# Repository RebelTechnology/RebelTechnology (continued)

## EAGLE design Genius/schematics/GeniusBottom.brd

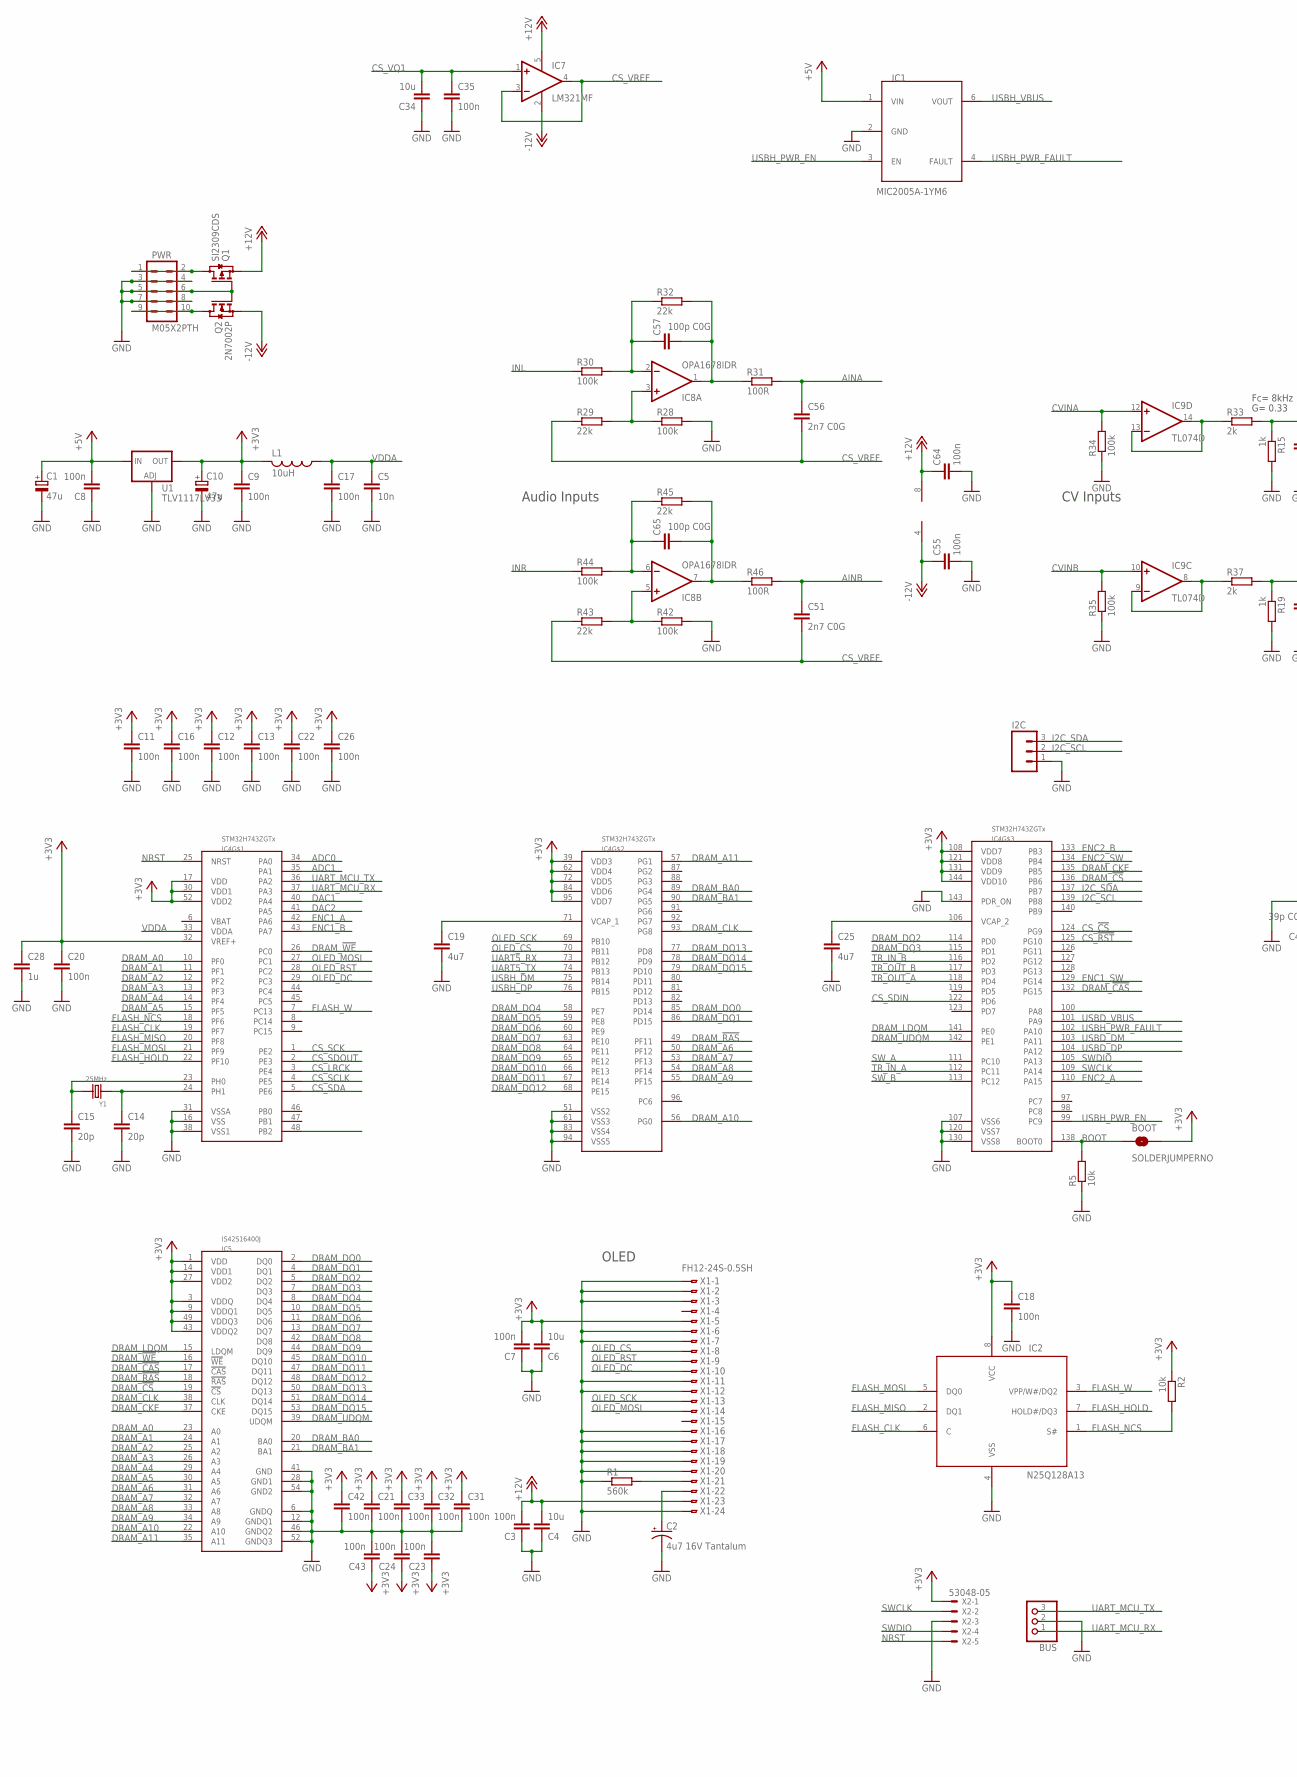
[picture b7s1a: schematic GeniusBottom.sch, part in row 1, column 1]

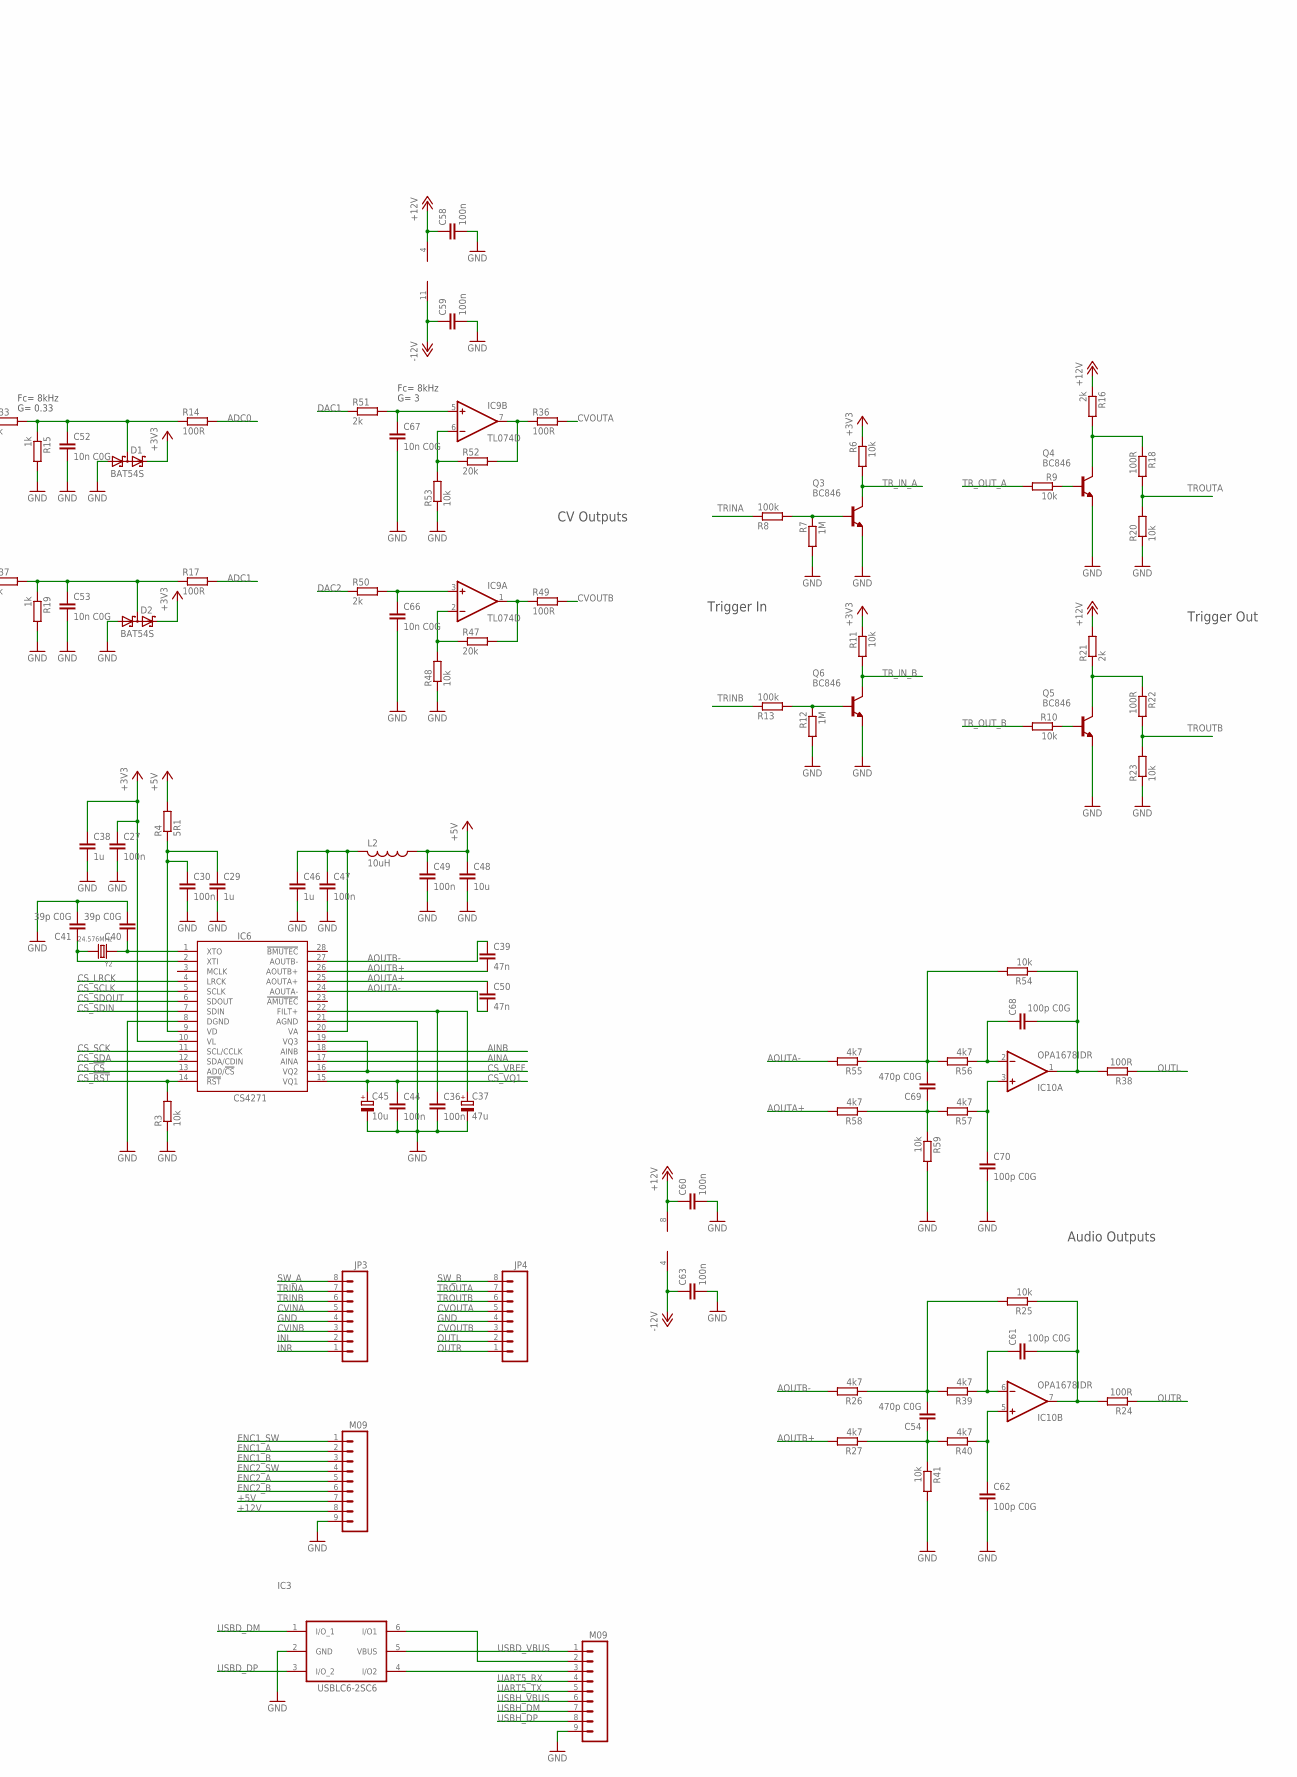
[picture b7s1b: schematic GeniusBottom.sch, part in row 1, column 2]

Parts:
BOOT: SOLDERJUMPERNO; SJ_2S-NO
BUS: CON-JST-1X03PH-TH; JST-B3B-PH-KL
C1, C10, C37: 47u; CPOL-5
C2: 4u7 16V Tantalum; EIA3216
C3, C7, C8, C9, C11, C12, C13, C16, C17, C18, C20, C21, C22, C23, C24, C26, C27, C30, C31, C32, C33, C35, C36, C42, C43, C44, C47, C49, C55, C58, C59, C60, C63, C64: 100n; C0603
C4, C6, C34, C48: 10u; C1206
C5: 10n; C0603
C14, C15: 20p; C0603
C19, C25: 4u7; C0603
C28, C29, C38, C46: 1u; C0603
C39, C50: 47n; C0603
C40, C41: 39p C0G; C0603
C45: 10u; CPOL-5
C51, C56: 2n7 C0G; C0603
C52, C53, C66, C67: 10n C0G; C0603
C54, C69: 470p C0G; C0603
C57, C61, C62, C65, C68, C70: 100p C0G; C0603
D1, D2: BAT54S; SOT23
I2C: M03PTH; 1X03
IC1: MIC2005A-1YM6; SOT23-6
IC2: N25Q128A13; SO8W
IC3: USBLC6-2SC6; SOT-23-6L
IC4: STM32H743ZGTx; QFP50P2200X2200X160-144N
IC5: IS42S16400J; TSOP54-400
IC6: CS4271; TSSOP28-0.65-9.7X4.4MM
IC7: LM321MF; SOT23-5
IC8, IC10: OPA1678IDR; SO08
IC9: TL074D; SO14
JP1, JP2: M09; 1X09
JP3, JP4: M081X08; 1X08
L1, L2: 10uH; 0603
PWR: M05X2PTH; AVR_ICSP
Q1: SI2309CDS; SOT23
Q2: 2N7002P; SOT23
Q3, Q4, Q5, Q6: BC846; SOT23
R1: 560k; 0603
R2, R3, R5, R6, R9, R10, R11, R20, R23, R25, R41, R48, R53, R54, R59: 10k; 0603
R4: 5R1; 0603
R7, R12: 1M; 0603
R8, R13, R28, R30, R34, R35, R42, R44: 100k; 0603
R14, R17, R18, R22, R24, R31, R36, R38, R46, R49: 100R; 0603
R15, R19: 1k; 0603
R16, R21, R33, R37, R50, R51: 2k; 0603
R26, R27, R39, R40, R55, R56, R57, R58: 4k7; 0603
R29, R32, R43, R45: 22k; 0603
R47, R52: 20k; 0603
U1: TLV1117LV33; SOT223
X1: FH12-24S-0.5SH
X2: 53048-05
Y1: 25MHz; X2-SMD-5.0X3.2X1.3MM
Y2: 24.576MHz; X2-SMD-5.0X3.2X1.3MM

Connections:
+3.3V: BOOT.2, C6.2, C7.2, C9.1, C10.+, C11.1, C12.1, C13.1, C16.1, C18.1, C20.1, C21.1, C22.1, C23.1, C24.1, C26.1, C27.1, C28.1, C31.1, C32.1, C33.1, C38.1, C42.1, C43.1, D1.2 (C2), D2.2 (C2), IC2.8 (VCC), IC4.17 (VDD), IC4.30 (VDD1), IC4.32 (VREF+), IC4.39 (VDD3), IC4.52 (VDD2), IC4.62 (VDD4), IC4.72 (VDD5), IC4.84 (VDD6), IC4.95 (VDD7), IC4.108 (VDD7), IC4.121 (VDD8), IC4.131 (VDD9), IC4.144 (VDD10), IC5.1 (VDD), IC5.3 (VDDQ), IC5.9 (VDDQ1), IC5.14 (VDD1), IC5.27 (VDD2), IC5.43 (VDDQ2), IC5.49 (VDDQ3), IC6.10 (VL), L1.2, R2.1, R6.1, R11.1, U1.4 (OUT), X1.5, X2.1
+5V: C1.+, C8.2, C48.1, C49.1, IC1.1 (VIN), JP2.7, L2.1, R4.2, U1.3 (IN)
+12V: C3.2, C4.2, C58.1, C60.1, C64.1, IC7.5 (V+), IC8.8 (V+), IC9.4 (V+), IC10.8 (V+), JP2.8, Q1.2 (S), R16.1, R21.2, X1.23
-12V: C55.1, C59.1, C63.1, IC7.2 (V-), IC8.4 (V-), IC9.11 (V-), IC10.4 (V-), Q2.2 (S)
ADC0: IC4.34 (PA0), R14.2
ADC1: IC4.35 (PA1), R17.2
AINA: C56.1, IC6.17 (AINA), R31.2
AINB: C51.1, IC6.18 (AINB), R46.2
ANALOG_OUTA: C68.2, IC10.1 (OUT), R38.2, R54.1
ANALOG_OUTB: C61.2, IC10.7 (OUT), R24.2, R25.1
AOUTA+: C50.1, IC6.25 (AOUTA+), R58.2
AOUTA-: C50.2, IC6.24 (AOUTA-), R55.2
AOUTB+: C39.2, IC6.26 (AOUTB+), R27.2
AOUTB-: C39.1, IC6.27 (AOUTB-), R26.2
BOOT: BOOT.1, IC4.138 (BOOT0), R5.2
CS_!CS: IC4.124 (PG9), IC6.13 (AD0/!CS)
CS_!RST: IC4.125 (PG10), IC6.14 (!RST), R3.2
CS_LRCK: IC4.3 (PE4), IC6.4 (LRCK)
CS_SCK: IC4.1 (PE2), IC6.11 (SCL/CCLK)
CS_SCLK: IC4.4 (PE5), IC6.5 (SCLK)
CS_SDA: IC4.5 (PE6), IC6.12 (SDA/CDIN)
CS_SDIN: IC4.122 (PD6), IC6.7 (SDIN)
CS_SDOUT: IC4.2 (PE3), IC6.6 (SDOUT)
CS_VQ1: C34.2, C35.1, C44.1, C45.+, IC6.15 (VQ1), IC7.1 (+IN)
CS_VREF: C51.2, C56.2, IC6.16 (VQ2), IC6.19 (VQ3), IC7.3 (-IN), IC7.4 (OUT), R29.1, R43.1
CVINA: IC9.12 (+IN), JP3.5, R34.2
CVINB: IC9.10 (+IN), JP3.3, R35.2
CVOUTA: JP4.5, R36.2
CVOUTB: JP4.3, R49.2
DAC1: IC4.40 (PA4), R51.1
DAC2: IC4.41 (PA5), R50.1
DRAM_!CAS: IC4.132 (PG15), IC5.17 (!CAS)
DRAM_!CS: IC4.136 (PB6), IC5.19 (!CS)
DRAM_!RAS: IC4.49 (PF11), IC5.18 (!RAS)
DRAM_!WE: IC4.26 (PC0), IC5.16 (!WE)
DRAM_A0: IC4.10 (PF0), IC5.23 (A0)
DRAM_A1: IC4.11 (PF1), IC5.24 (A1)
DRAM_A2: IC4.12 (PF2), IC5.25 (A2)
DRAM_A3: IC4.13 (PF3), IC5.26 (A3)
DRAM_A4: IC4.14 (PF4), IC5.29 (A4)
DRAM_A5: IC4.15 (PF5), IC5.30 (A5)
DRAM_A6: IC4.50 (PF12), IC5.31 (A6)
DRAM_A7: IC4.53 (PF13), IC5.32 (A7)
DRAM_A8: IC4.54 (PF14), IC5.33 (A8)
DRAM_A9: IC4.55 (PF15), IC5.34 (A9)
DRAM_A10: IC4.56 (PG0), IC5.22 (A10)
DRAM_A11: IC4.57 (PG1), IC5.35 (A11)
DRAM_BA0: IC4.89 (PG4), IC5.20 (BA0)
DRAM_BA1: IC4.90 (PG5), IC5.21 (BA1)
DRAM_CKE: IC4.135 (PB5), IC5.37 (CKE)
DRAM_CLK: IC4.93 (PG8), IC5.38 (CLK)
DRAM_DQ0: IC4.85 (PD14), IC5.2 (DQ0)
DRAM_DQ1: IC4.86 (PD15), IC5.4 (DQ1)
DRAM_DQ2: IC4.114 (PD0), IC5.5 (DQ2)
DRAM_DQ3: IC4.115 (PD1), IC5.7 (DQ3)
DRAM_DQ4: IC4.58 (PE7), IC5.8 (DQ4)
DRAM_DQ5: IC4.59 (PE8), IC5.10 (DQ5)
DRAM_DQ6: IC4.60 (PE9), IC5.11 (DQ6)
DRAM_DQ7: IC4.63 (PE10), IC5.13 (DQ7)
DRAM_DQ8: IC4.64 (PE11), IC5.42 (DQ8)
DRAM_DQ9: IC4.65 (PE12), IC5.44 (DQ9)
DRAM_DQ10: IC4.66 (PE13), IC5.45 (DQ10)
DRAM_DQ11: IC4.67 (PE14), IC5.47 (DQ11)
DRAM_DQ12: IC4.68 (PE15), IC5.48 (DQ12)
DRAM_DQ13: IC4.77 (PD8), IC5.50 (DQ13)
DRAM_DQ14: IC4.78 (PD9), IC5.51 (DQ14)
DRAM_DQ15: IC4.79 (PD10), IC5.53 (DQ15)
DRAM_LDQM: IC4.141 (PE0), IC5.15 (LDQM)
DRAM_UDQM: IC4.142 (PE1), IC5.39 (UDQM)
ENC1_A: IC4.42 (PA6), JP2.2
ENC1_B: IC4.43 (PA7), JP2.3
ENC1_SW: IC4.129 (PG14), JP2.1
ENC2_A: IC4.110 (PA15), JP2.5
ENC2_B: IC4.133 (PB3), JP2.6
ENC2_SW: IC4.134 (PB4), JP2.4
FLASH_CLK: IC2.6 (C), IC4.19 (PF7)
FLASH_HOLD: IC2.7 (HOLD#/DQ3), IC4.22 (PF10)
FLASH_MISO: IC2.2 (DQ1), IC4.20 (PF8)
FLASH_MOSI: IC2.5 (DQ0), IC4.21 (PF9)
FLASH_NCS: IC2.1 (S#), IC4.18 (PF6), R2.2
FLASH_W: IC2.3 (VPP/W#/DQ2), IC4.7 (PC13)
GND: BUS.2, C1.-, C2.C (-), C3.1, C4.1, C5.2, C6.1, C7.1, C8.1, C9.2, C10.-, C11.2, C12.2, C13.2, C14.2, C15.2, C16.2, C17.2, C18.2, C19.2, C20.2, C21.2, C22.2, C23.2, C24.2, C25.2, C26.2, C27.2, C28.2, C29.2, C30.2, C31.2, C32.2, C33.2, C34.1, C35.2, C36.2, C37.-, C38.2, C40.2, C41.2, C42.2, C43.2, C44.2, C45.-, C46.2, C47.2, C48.2, C49.2, C52.2, C53.2, C55.2, C58.2, C59.2, C60.2, C62.2, C63.2, C64.2, C66.2, C67.2, C70.2, D1.1 (A1), D2.1 (A1), I2C.1, IC1.2 (GND), IC2.4 (VSS), IC3.2 (GND), IC4.16 (VSS), IC4.31 (VSSA), IC4.38 (VSS1), IC4.51 (VSS2), IC4.61 (VSS3), IC4.83 (VSS4), IC4.94 (VSS5), IC4.107 (VSS6), IC4.120 (VSS7), IC4.130 (VSS8), IC4.143 (PDR_ON), IC5.6 (GNDQ), IC5.12 (GNDQ1), IC5.28 (GND1), IC5.41 (GND), IC5.46 (GNDQ2), IC5.52 (GNDQ3), IC5.54 (GND2), IC6.8 (DGND), IC6.21 (AGND), JP1.9, JP2.9, JP3.4, JP4.4, PWR.3, PWR.4, PWR.5, PWR.6, PWR.7, PWR.8, Q1.1 (G), Q2.1 (G), Q3.2 (E), Q4.2 (E), Q5.2 (E), Q6.2 (E), R1.1, R3.1, R5.1, R7.2, R12.2, R15.2, R19.2, R20.1, R23.1, R28.2, R34.1, R35.1, R41.2, R42.2, R48.1, R53.1, R59.2, U1.1 (ADJ), X1.1, X1.2, X1.3, X1.6, X1.7, X1.11, X1.12, X1.16, X1.17, X1.18, X1.19, X1.20, X1.24, X2.3
I2C_SCL: I2C.2, IC4.139 (PB8)
I2C_SDA: I2C.3, IC4.137 (PB7)
INL: JP3.2, R30.1
INR: JP3.1, R44.1
unnamed: C69.1, R57.2, R58.1, R59.1
unnamed: C52.1, D1.3 (C1A2), R14.1, R15.1, R33.2
unnamed: C46.1, C47.1, IC6.20 (VA), L2.2
unnamed: IC9.7 (OUT), R36.1, R52.2
unnamed: IC9.8 (OUT), IC9.9 (-IN), R37.1
unnamed: C2.A (+), X1.22
unnamed: PWR.9, PWR.10, Q2.3 (D)
unnamed: R1.2, X1.21
unnamed: PWR.1, PWR.2, Q1.3 (D)
unnamed: C69.2, R54.2, R55.1, R56.2
unnamed: C14.1, IC4.24 (PH1), Y1.1
unnamed: IC9.2 (-IN), R47.1, R48.2
unnamed: C68.1, IC10.2 (-IN), R56.1
unnamed: C70.1, IC10.3 (+IN), R57.1
unnamed: IC9.6 (-IN), R52.1, R53.2
unnamed: C15.1, IC4.23 (PH0), Y1.2
unnamed: C40.1, IC6.1 (XTO), Y2.1
unnamed: IC3.6 (I/O1), JP1.2
unnamed: C36.1, C37.+, IC6.22 (FILT+)
unnamed: C41.1, IC6.2 (XTI), Y2.2
unnamed: C53.1, D2.3 (C1A2), R17.1, R19.1, R37.2
unnamed: C54.1, R27.1, R40.2, R41.1
unnamed: C54.2, R25.2, R26.1, R39.2
unnamed: C61.1, IC10.6 (-IN), R39.1
unnamed: C62.1, IC10.5 (+IN), R40.1
unnamed: IC9.13 (-IN), IC9.14 (OUT), R33.1
unnamed: C66.1, IC9.3 (+IN), R50.2
unnamed: IC9.1 (OUT), R47.2, R49.1
unnamed: C25.1, IC4.106 (VCAP_2)
unnamed: C19.1, IC4.71 (VCAP_1)
unnamed: IC8.3 (+IN), R28.1, R29.2
unnamed: Q6.1 (B), R12.1, R13.2
unnamed: C57.1, IC8.2 (-IN), R30.2, R32.1
unnamed: Q5.1 (B), R10.1
unnamed: C57.2, IC8.1 (OUT), R31.1, R32.2
unnamed: Q5.3 (C), R21.1, R22.1
unnamed: IC8.5 (+IN), R42.1, R43.2
unnamed: C65.1, IC8.6 (-IN), R44.2, R45.1
unnamed: C67.1, IC9.5 (+IN), R51.2
unnamed: C65.2, IC8.7 (OUT), R45.2, R46.1
unnamed: Q4.1 (B), R9.1
unnamed: Q4.3 (C), R16.2, R18.1
unnamed: Q3.1 (B), R7.1, R8.2
unnamed: IC3.4 (I/O2), JP1.3
NRST: IC4.25 (NRST), X2.5
OLED_CS: IC4.70 (PB11), X1.8
OLED_DC: IC4.29 (PC3), X1.10
OLED_MOSI: IC4.27 (PC1), X1.14
OLED_RST: IC4.28 (PC2), X1.9
OLED_SCK: IC4.69 (PB10), X1.13
OUTL: JP4.2, R38.1
OUTR: JP4.1, R24.1
SWCLK: IC4.109 (PA14), X2.2
SWDIO: IC4.105 (PA13), X2.4
SW_A: IC4.111 (PC10), JP3.8
SW_B: IC4.113 (PC12), JP4.8
TRINA: JP3.7, R8.1
TRINB: JP3.6, R13.1
TROUTA: JP4.7, R18.2, R20.2
TROUTB: JP4.6, R22.2, R23.2
TR_IN_A: IC4.112 (PC11), Q3.3 (C), R6.2
TR_IN_B: IC4.116 (PD2), Q6.3 (C), R11.2
TR_OUT_A: IC4.118 (PD4), R9.2
TR_OUT_B: IC4.117 (PD3), R10.2
UART5_RX: IC4.73 (PB12), JP1.4
UART5_TX: IC4.74 (PB13), JP1.5
UART_MCU_RX: BUS.1, IC4.37 (PA3)
UART_MCU_TX: BUS.3, IC4.36 (PA2)
USBD_DM: IC3.1 (I/O_1), IC4.103 (PA11)
USBD_DP: IC3.3 (I/O_2), IC4.104 (PA12)
USBD_VBUS: IC3.5 (VBUS), IC4.101 (PA9), JP1.1
USBH_DM: IC4.75 (PB14), JP1.7
USBH_DP: IC4.76 (PB15), JP1.8
USBH_PWR_EN: IC1.3 (EN), IC4.99 (PC9)
USBH_PWR_FAULT: IC1.4 (FAULT), IC4.102 (PA10)
USBH_VBUS: IC1.6 (VOUT), JP1.6
VD: C29.1, C30.1, IC6.9 (VD), R4.1
VDDA: C5.1, C17.1, IC4.33 (VDDA), L1.1

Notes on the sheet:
Audio Outputs
Audio Inputs
CV Inputs
G= 0.33
CV Outputs
Fc= 8kHz
Trigger In
Trigger Out
OLED
G= 3

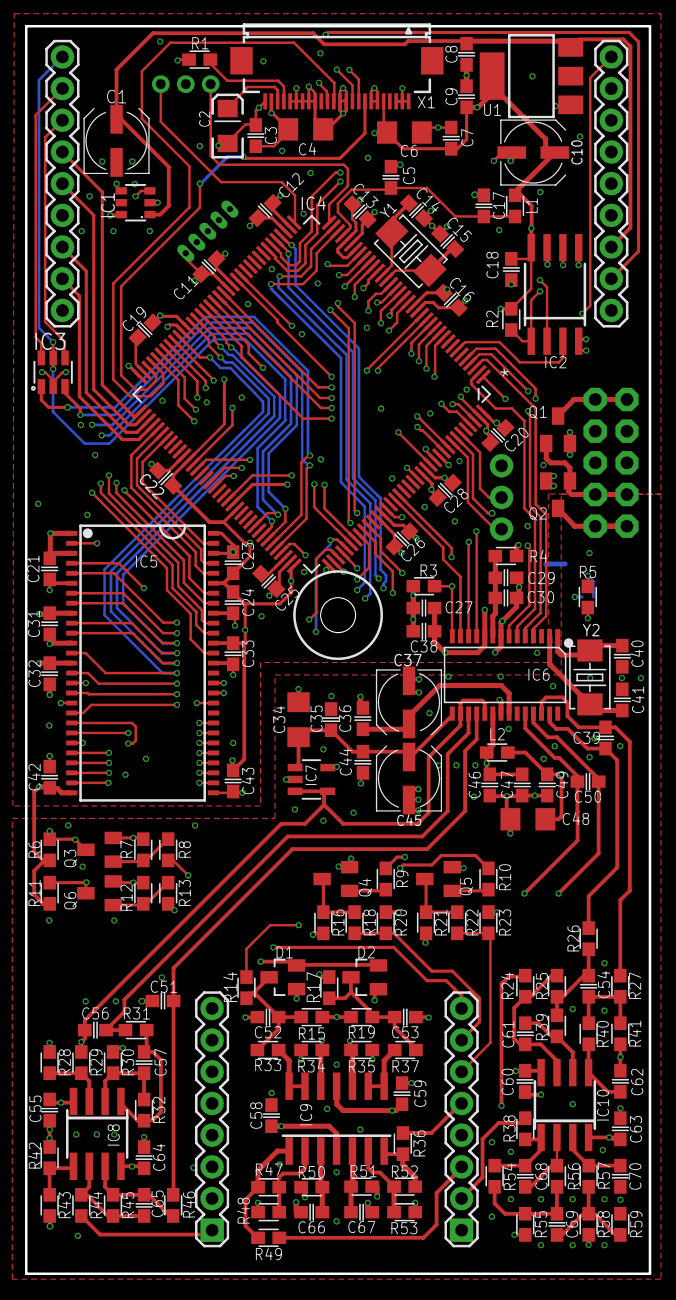
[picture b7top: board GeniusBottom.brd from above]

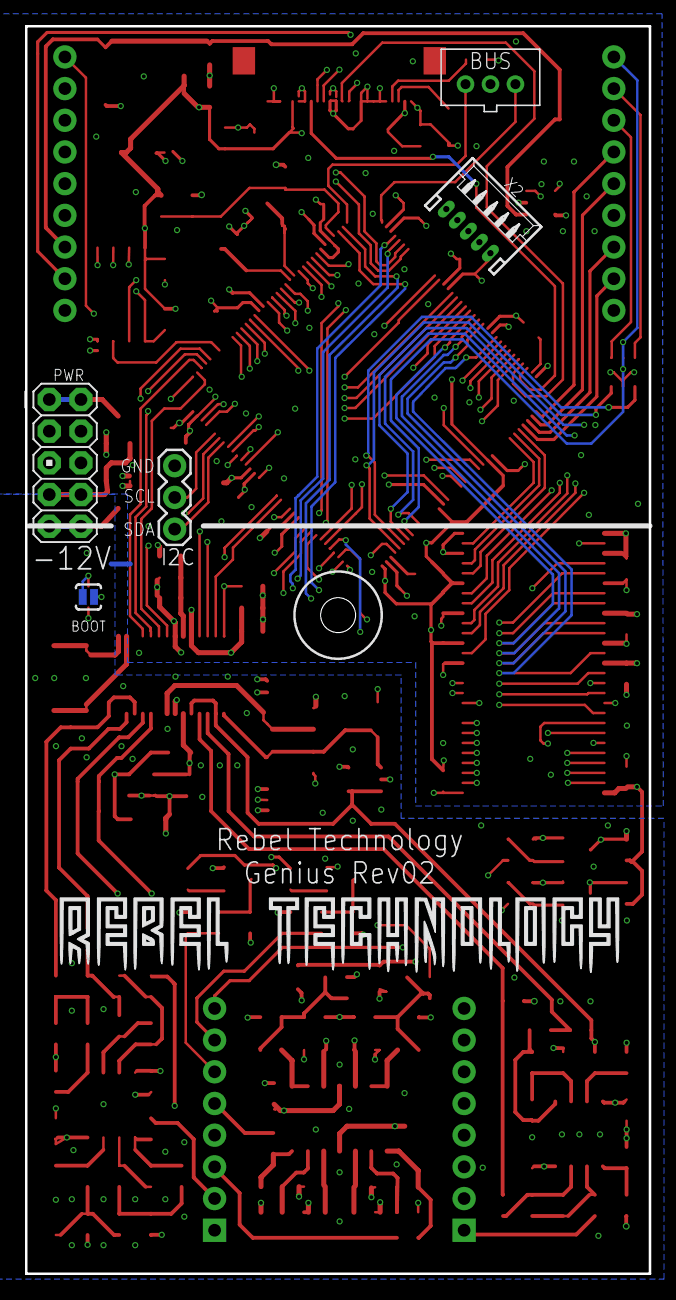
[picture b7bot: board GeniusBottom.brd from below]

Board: 4 copper layers, 50.0 x 100.0 mm, 162 parts (5 on the bottom side), 164 nets.

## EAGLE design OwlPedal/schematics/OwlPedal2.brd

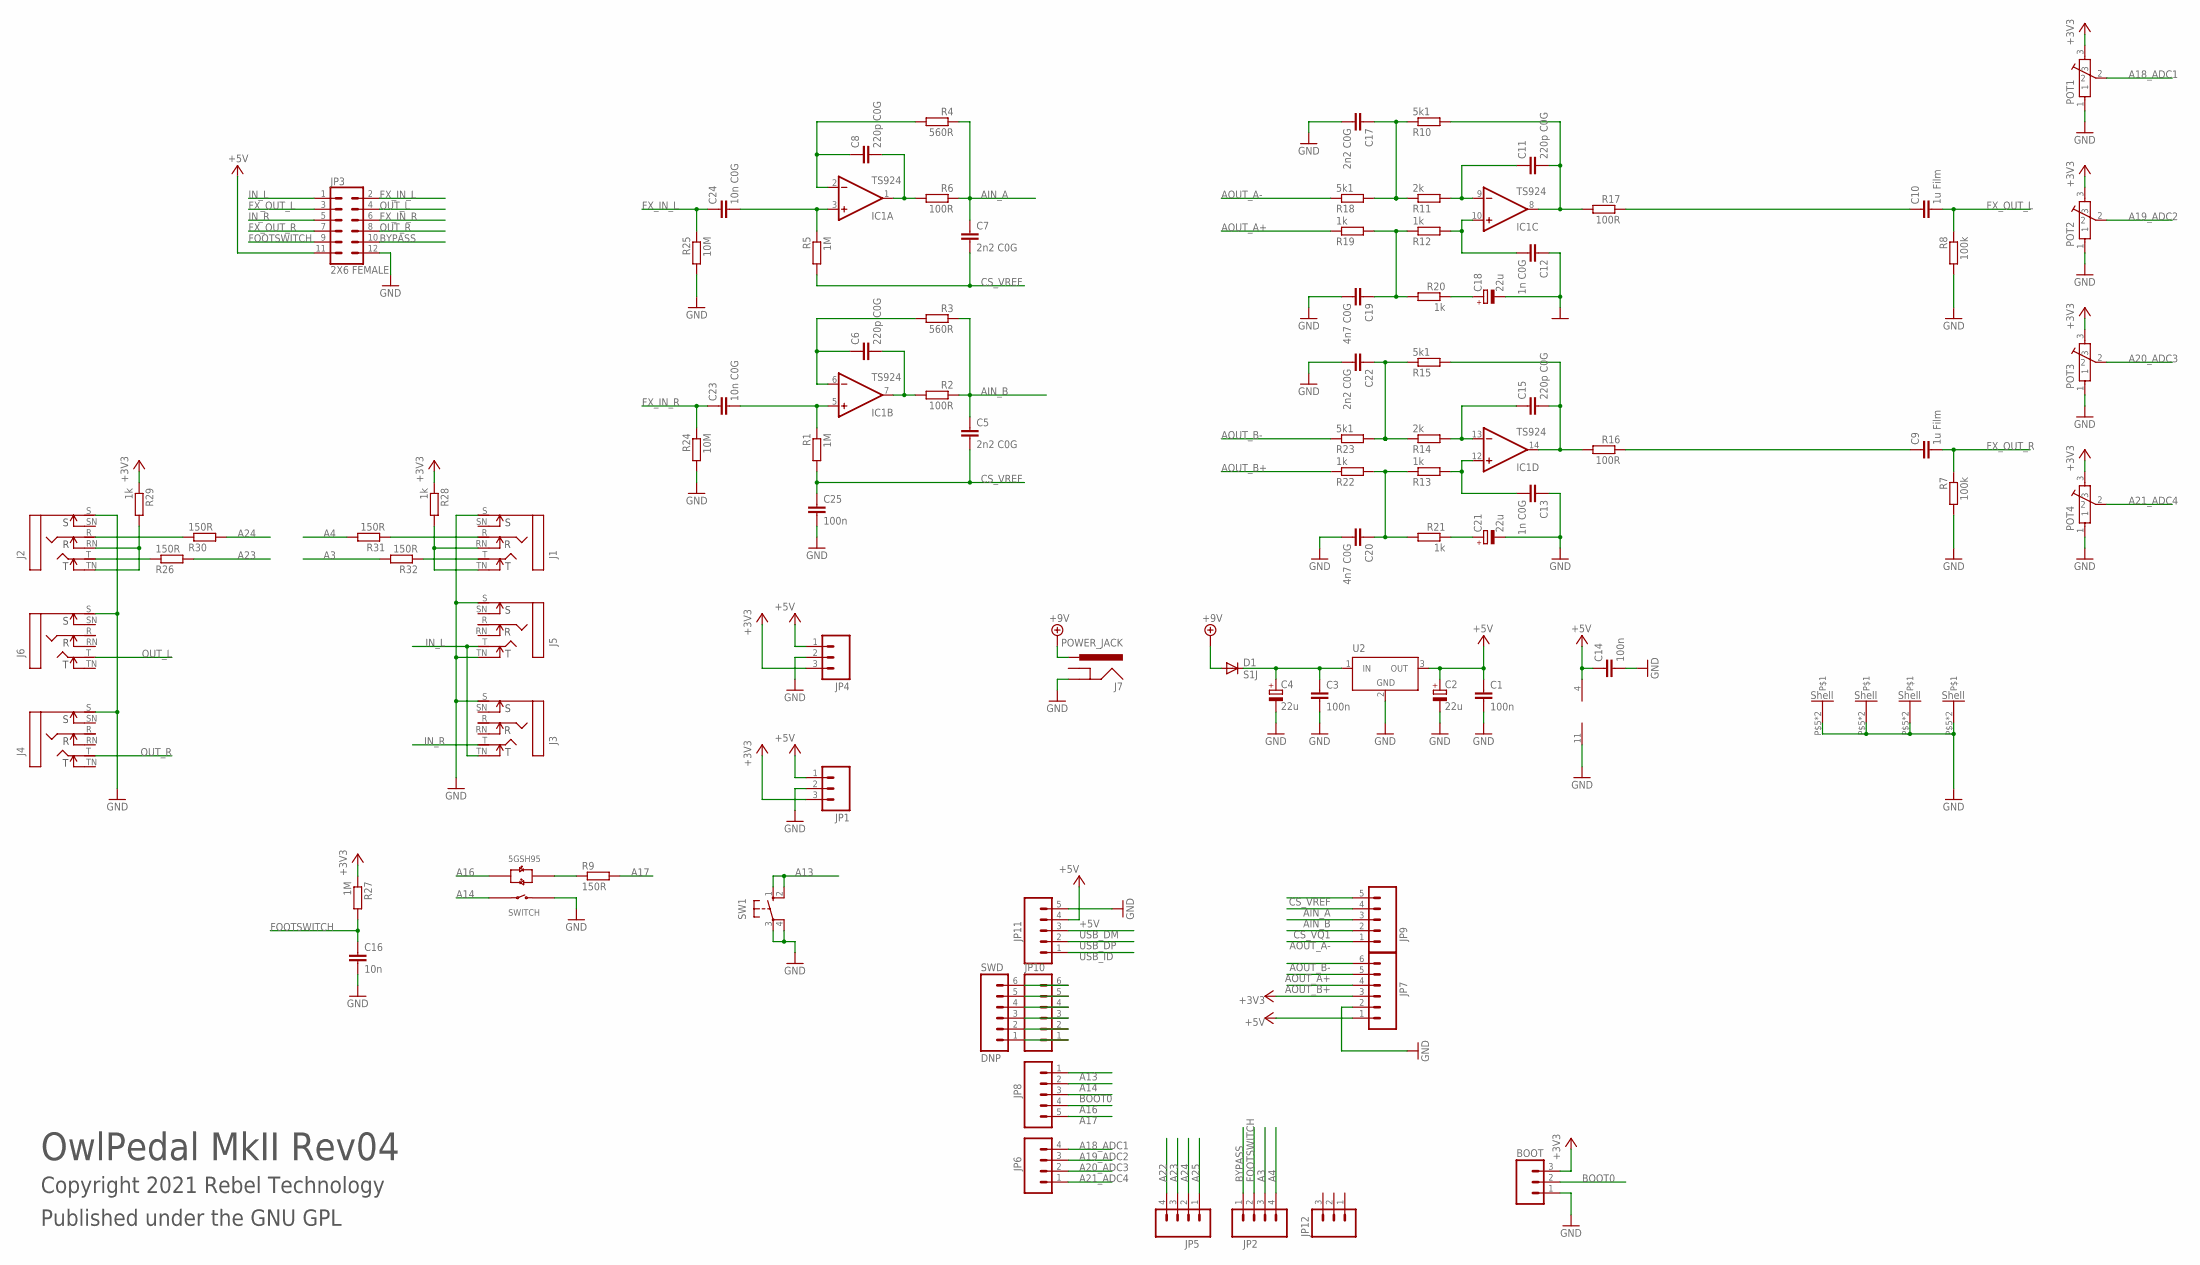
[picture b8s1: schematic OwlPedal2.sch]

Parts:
BOOT: M03PTH; 1X03
C1, C3, C14, C25: 100n; C0603
C2, C4, C18, C21: 22u; CPOL-5
C5, C7, C17, C22: 2n2 C0G; C0603
C6, C8, C11, C15: 220p C0G; C0603
C9, C10: 1u Film; C1210
C12, C13: 1n C0G; C0603
C16: 10n; C0603
C19, C20: 4n7 C0G; C0603
C23, C24: 10n C0G; C0603
D1: S1J; SMA-DIODE
IC1: TS924; SO14
J1, J2, J3, J4, J5, J6: NEUTRIK_NMJ6HCD2; NMJ6HCD2
J7: POWER_JACK; DC_JACK_SLOT
JP1, JP4, JP12: M03PTH; 1X03
JP2, JP5, JP6: M04PTH; 1X04
JP3: 2X6 FEMALE; 2X6
JP7, JP10: M06SIP; 1X06
JP8, JP9, JP11: M05PTH; 1X05
POT1, POT2, POT3, POT4: POT-ALPS-RK09L1140
R1, R5, R27: 1M; 0603
R2, R6, R16, R17: 100R; 0603
R3, R4: 560R; 0603
R7, R8: 100k; 0603
R9, R26, R30, R31, R32: 150R; 0603
R10, R15, R18, R23: 5k1; 0603
R11, R14: 2k; 0603
R12, R13, R19, R20, R21, R22, R28, R29: 1k; 0603
R24, R25: 10M; 0603
SW1: 10-XX; B3F-10XX
SW2: 5GTH9
SWD: DNP; 1X06
U2: TSR-1-2450

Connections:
+3V3: BOOT.3, JP1.3, JP4.3, JP7.3, POT1.3, POT2.3, POT3.3, POT4.3, R27.1, R28.1, R29.1
+5V: C1.1, C2.+, C14.1, IC1.4 (V+), JP1.1, JP3.11, JP4.1, JP7.1, JP11.4, U2.3 (OUT)
+9V: D1.A, J7.PWR
A3: JP2.3, R32.2
A4: JP2.4, R31.2
A13: JP8.1, SW1.1 (S), SW1.2 (S1)
A14: JP8.2, SW2.4 (SWITCH_A)
A16: JP8.4, SW2.-2 (LED_G+)
A17: JP8.5, R9.2
A18_ADC1: JP6.4, POT1.2
A19_ADC2: JP6.3, POT2.2
A20_ADC3: JP6.2, POT3.2
A21_ADC4: JP6.1, POT4.2
A22: JP5.4
A23: JP5.3, R26.2
A24: JP5.2, R30.2
A25: JP5.1
AIN_A: C7.1, JP9.4, R4.1, R6.1
AIN_B: C5.1, JP9.3, R2.1, R3.1
AOUT_A+: JP7.5, R19.1
AOUT_A-: JP9.1, R18.1
AOUT_B+: JP7.4, R22.1
AOUT_B-: JP7.6, R23.1
BOOT0: BOOT.2, JP8.3
BYPASS: JP2.1, JP3.10
CS_VQ1: JP9.2
CS_VREF: C5.2, C7.2, C25.1, JP9.5, R1.2, R5.2
DC_IN_L: C24.1, IC1.3 (+IN), R5.1
DC_IN_R: C23.1, IC1.5 (+IN), R1.1
FOOTSWITCH: C16.1, JP2.2, JP3.9, R27.2
FX_IN_L: C24.2, JP3.2, R25.1
FX_IN_R: C23.2, JP3.6, R24.1
FX_OUT_L: C10.2, JP3.3, R8.1
FX_OUT_R: C9.2, JP3.7, R7.1
GND: BOOT.1, C1.2, C2.-, C3.2, C4.-, C12.1, C13.1, C14.2, C16.2, C17.2, C18.-, C19.2, C20.2, C21.-, C22.2, C25.2, IC1.11 (V-), J1.S, J2.S, J3.S, J4.S, J5.S, J5.TN, J6.S, J7.GND, JP1.2, JP3.12, JP4.2, JP7.2, JP11.5, POT1.1, POT1.P$5, POT1.P$6, POT2.1, POT2.P$5, POT2.P$6, POT3.1, POT3.P$5, POT3.P$6, POT4.1, POT4.P$5, POT4.P$6, R7.2, R8.2, R24.2, R25.2, SW1.3, SW1.4 (P1), SW2.1 (SWITCH_B), U2.2 (GND)
IN_L: J3.TN, J5.T, JP3.1
IN_R: J3.T, JP3.5
unnamed: J1.RN, J1.TN, R28.2
unnamed: J2.R, R30.1
unnamed: JP10.1, SWD.1
unnamed: J2.RN, J2.TN, R29.2
unnamed: JP10.2, SWD.2
unnamed: JP10.3, SWD.3
unnamed: JP10.4, SWD.4
unnamed: JP10.5, SWD.5
unnamed: JP10.6, SWD.6
unnamed: R9.1, SW2.+3 (LED_R+)
unnamed: J1.R, R31.1
unnamed: C17.1, R10.1, R11.1, R18.2
unnamed: C6.1, IC1.6 (-IN), R3.2
unnamed: J1.T, R32.1
unnamed: C11.1, IC1.9 (-IN), R11.2
unnamed: C12.2, IC1.10 (+IN), R12.2
unnamed: C19.1, R12.1, R19.2, R20.2
unnamed: C15.1, IC1.13 (-IN), R14.2
unnamed: C13.2, IC1.12 (+IN), R13.2
unnamed: C20.1, R13.1, R21.2, R22.2
unnamed: C8.1, IC1.2 (-IN), R4.2
unnamed: C8.2, IC1.1 (OUT), R6.2
unnamed: C22.1, R14.1, R15.1, R23.2
unnamed: C6.2, IC1.7 (OUT), R2.2
unnamed: J2.T, R26.1
unnamed: C11.2, IC1.8 (OUT), R10.2, R17.2
unnamed: C18.+, R20.1
unnamed: C9.1, R16.1
unnamed: C21.+, R21.1
unnamed: C15.2, IC1.14 (OUT), R15.2, R16.2
unnamed: C10.1, R17.1
unnamed: C3.1, C4.+, D1.C, U2.1 (IN)
OUT_L: J6.T, JP3.4
OUT_R: J4.T, JP3.8
USB_DM: JP11.3
USB_DP: JP11.2
USB_ID: JP11.1

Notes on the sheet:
OwlPedal MkII Rev04
Copyright 2021 Rebel Technology
Published under the GNU GPL

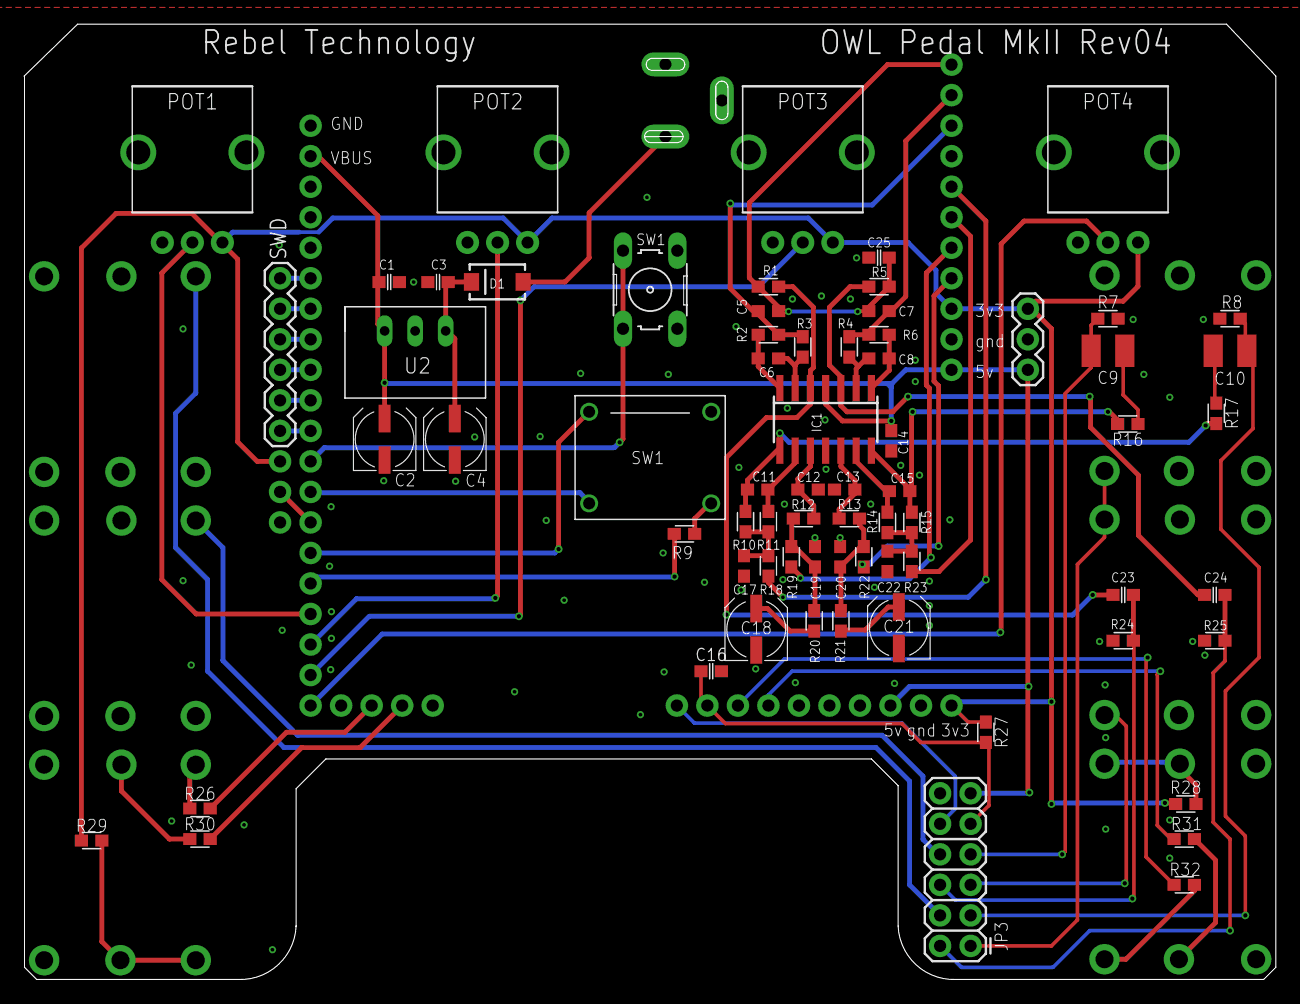
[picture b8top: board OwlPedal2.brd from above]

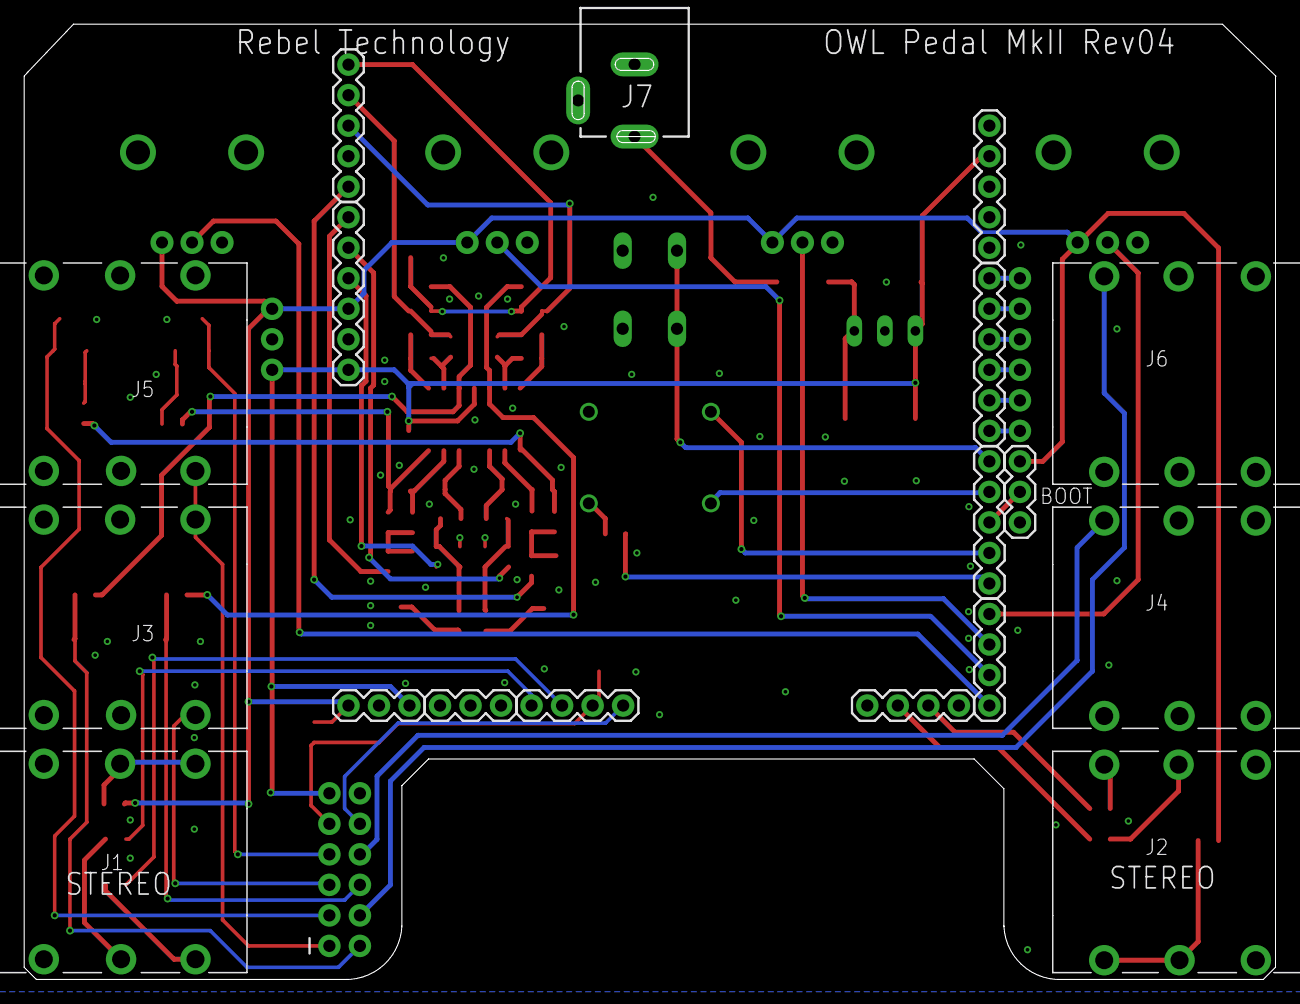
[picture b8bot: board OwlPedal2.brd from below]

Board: 2 copper layers, 104.2 x 79.5 mm, 87 parts (18 on the bottom side), 68 nets.
